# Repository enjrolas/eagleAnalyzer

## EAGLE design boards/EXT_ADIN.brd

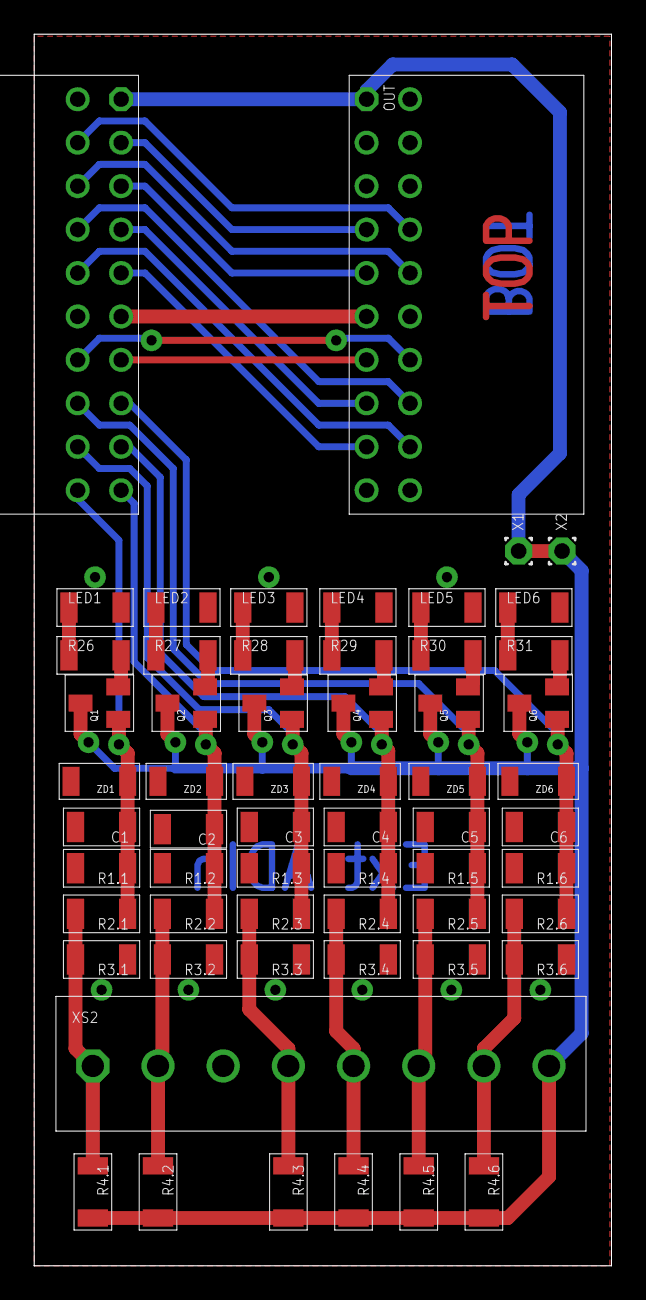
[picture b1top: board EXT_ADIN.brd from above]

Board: 2 copper layers, 33.8 x 72.0 mm, 59 parts (0 on the bottom side), 38 nets.

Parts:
C1, C2, C3, C4, C5, C6: 33n; 1206
IN: EF20; FE10-2WS
LED1, LED2: GREEN; 1206
LED3, LED4, LED5, LED6: YELLOW; 1206
OUT: MF20; ML20LS
Q1, Q2, Q3, Q4, Q5, Q6: BSS139; SOT23
R1.1, R1.2: 3k3; 1206
R1.3, R1.4, R1.5, R1.6: 39k; 1206
R2.1, R2.2: 6k8; 1206
R2.3, R2.4, R2.5, R2.6: 10k; 1206
R3.1, R3.5, R3.6, R4.1, R4.2, R4.3, R4.4: n.b.; 1206
R3.2: 560R; 1206
R3.3, R3.4, R4.5, R4.6: 3k6; 1206
R26, R27, R28, R29, R30, R31: 470R; 1206
X1, X2: T1.6/0.9
XS2: 1727078; SCR_381_8
ZD1, ZD2, ZD3, ZD4, ZD5, ZD6: SOD80

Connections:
3V3: IN.P$11, OUT.P$11
AI6: C1.1, IN.P$20, Q1.1, R1.1.1, R2.1.1, ZD1.C
AI7: C2.1, IN.P$19, Q2.1, R1.2.1, R2.2.1, ZD2.C
GND: C1.2, C2.2, C3.2, C4.2, C5.2, C6.2, IN.P$2, IN.P$12, LED1.2, LED2.2, LED3.2, LED4.2, LED5.2, LED6.2, OUT.P$2, OUT.P$12, R1.1.2, R1.2.2, R1.3.2, R1.4.2, R1.5.2, R1.6.2, R3.1.1, R3.2.1, R3.3.1, R3.4.1, R3.5.1, R3.6.1, XS2.P$3, ZD1.A, ZD2.A, ZD3.A, ZD4.A, ZD5.A, ZD6.A
unnamed: R2.2.2, R3.2.2, R4.2.1, XS2.P$2
unnamed: R2.3.2, R3.3.2, R4.3.1, XS2.P$4
unnamed: R2.1.2, R3.1.2, R4.1.1, XS2.P$1
unnamed: R2.4.2, R3.4.2, R4.4.1, XS2.P$5
unnamed: R2.5.2, R3.5.2, R4.5.1, XS2.P$6
unnamed: R2.6.2, R3.6.2, R4.6.1, XS2.P$7
unnamed: LED1.1, R26.1
unnamed: Q1.2, R26.2
unnamed: LED2.1, R27.1
unnamed: Q2.2, R27.2
unnamed: LED3.1, R28.1
unnamed: Q3.2, R28.2
unnamed: LED4.1, R29.1
unnamed: Q4.2, R29.2
unnamed: LED5.1, R30.1
unnamed: Q5.2, R30.2
unnamed: LED6.1, R31.1
unnamed: Q6.2, R31.2
PC0: C3.1, IN.P$18, Q3.1, R1.3.1, R2.3.1, ZD3.C
PC1: C4.1, IN.P$17, Q4.1, R1.4.1, R2.4.1, ZD4.C
PC2: C5.1, IN.P$16, Q5.1, R1.5.1, R2.5.1, ZD5.C
PC3: C6.1, IN.P$15, Q6.1, R1.6.1, R2.6.1, ZD6.C
PC4/SDA: IN.P$14, OUT.P$14
PC5/SCL: IN.P$13, OUT.P$13
PD0: IN.P$10, OUT.P$18
PD1: IN.P$9, OUT.P$17
PD2: IN.P$8, OUT.P$16
PD3: IN.P$7, OUT.P$15
PD4: IN.P$6, OUT.P$10
PD5: IN.P$5, OUT.P$9
PD6: IN.P$4, OUT.P$8
PD7: IN.P$3, OUT.P$7
VCC: Q1.3, Q2.3, Q3.3, Q4.3, Q5.3, Q6.3, R4.1.2, R4.2.2, R4.3.2, R4.4.2, R4.5.2, R4.6.2, X2.1, XS2.P$8
VIN: IN.P$1, OUT.P$1, X1.1

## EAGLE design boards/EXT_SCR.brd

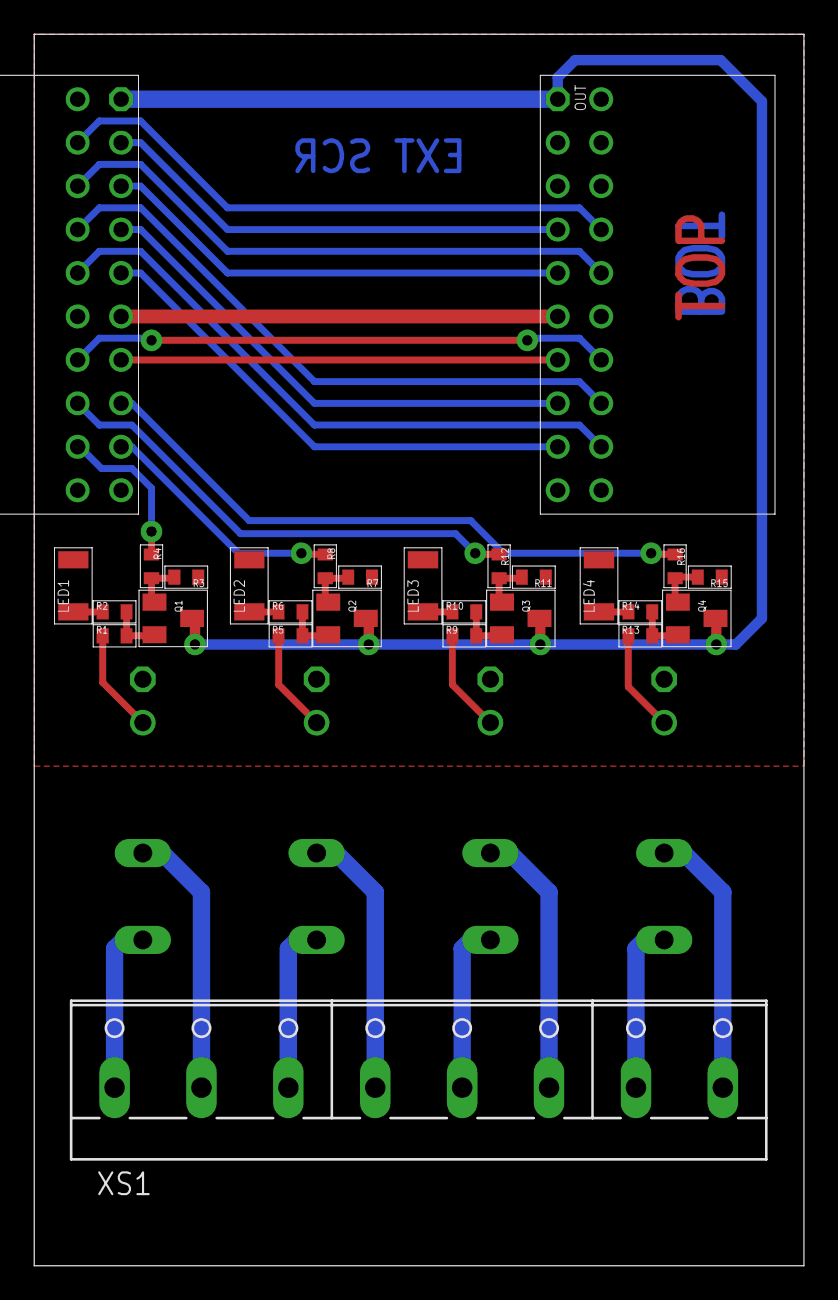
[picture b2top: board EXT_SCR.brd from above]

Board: 2 copper layers, 45.0 x 72.0 mm, 31 parts (0 on the bottom side), 41 nets.

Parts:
IN: EF20; FE10-2WS
LED1, LED2, LED3, LED4: LEDR; 1206
OUT: MF20; ML20LS
Q1, Q2, Q3, Q4: BC817; SOT23
R1, R5, R9, R13: 47R; 0603
R2, R6, R10, R14: 180R; 0603
R3, R7, R11, R15: 10k; 0603
R4, R8, R12, R16: 1k; 0603
SCR1, SCR2, SCR3, SCR4: S202S02; S202
XS1: 1729186; W237-8P

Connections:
3V3: IN.P$11, OUT.P$11
GND: IN.P$2, IN.P$12, LED1.2, LED2.2, LED3.2, LED4.2, OUT.P$2, OUT.P$12, R3.1, R7.1, R11.1, R15.1, SCR1.LED-, SCR2.LED-, SCR3.LED-, SCR4.LED-
unnamed: R1.1, SCR1.LED+
unnamed: LED1.1, R2.1
unnamed: Q1.2, R1.2, R2.2
unnamed: Q1.1, R3.2, R4.2
unnamed: R5.1, SCR2.LED+
unnamed: LED2.1, R6.1
unnamed: Q2.2, R5.2, R6.2
unnamed: Q2.1, R7.2, R8.2
unnamed: R9.1, SCR3.LED+
unnamed: LED3.1, R10.1
unnamed: Q3.2, R9.2, R10.2
unnamed: Q3.1, R11.2, R12.2
unnamed: R13.1, SCR4.LED+
unnamed: LED4.1, R14.1
unnamed: Q4.2, R13.2, R14.2
unnamed: Q4.1, R15.2, R16.2
unnamed: SCR1.AC1, XS1.1
unnamed: SCR1.AC2, XS1.2
unnamed: SCR2.AC1, XS1.3
unnamed: SCR2.AC2, XS1.4
unnamed: SCR3.AC1, XS1.5
unnamed: SCR3.AC2, XS1.6
unnamed: SCR4.AC2, XS1.8
unnamed: SCR4.AC1, XS1.7
PC0: IN.P$18, R4.1
PC1: IN.P$17, R8.1
PC2: IN.P$16, R12.1
PC3: IN.P$15, R16.1
PC4/SDA: IN.P$14, OUT.P$14
PC5/SCL: IN.P$13, OUT.P$13
PD0: IN.P$10, OUT.P$18
PD1: IN.P$9, OUT.P$17
PD2: IN.P$8, OUT.P$16
PD3: IN.P$7, OUT.P$15
PD4: IN.P$6, OUT.P$10
PD5: IN.P$5, OUT.P$9
PD6: IN.P$4, OUT.P$8
PD7: IN.P$3, OUT.P$7
VCC: IN.P$1, OUT.P$1, Q1.3, Q2.3, Q3.3, Q4.3

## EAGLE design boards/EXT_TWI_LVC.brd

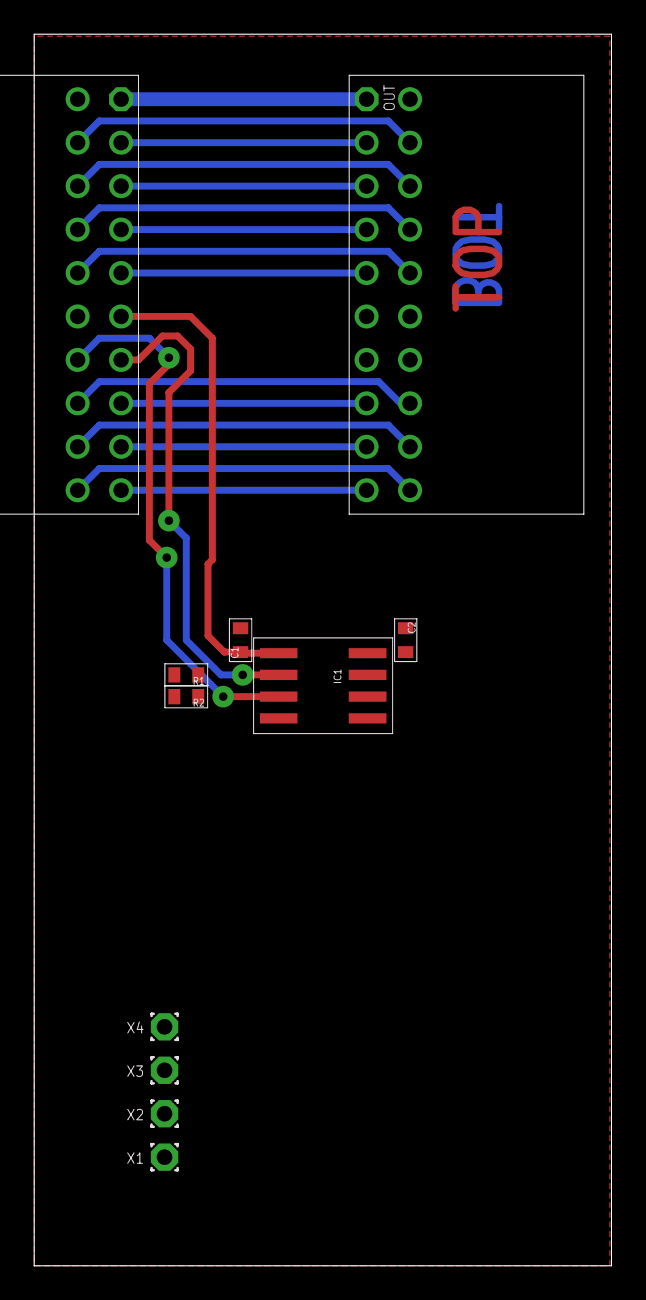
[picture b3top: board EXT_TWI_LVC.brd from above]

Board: 2 copper layers, 33.8 x 72.0 mm, 11 parts (0 on the bottom side), 22 nets.

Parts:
C1, C2: 100n; 0603
IC1: SOIC8
IN: EF20; FE10-2WS
OUT: MF20; ML20LS
R1, R2: 0603
X1, X2, X3, X4: T1.6/0.9

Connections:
GND: C1.2, C2.1, IC1.4, IN.P$2, IN.P$12, OUT.P$2, OUT.P$12, X1.1
unnamed: IN.P$20, OUT.P$20
unnamed: IN.P$19, OUT.P$19
unnamed: C2.2, IC1.8, OUT.P$11
PC0: IN.P$18, OUT.P$18
PC1: IN.P$17, OUT.P$17
PC2: IN.P$16, OUT.P$16
PC3: IN.P$15, OUT.P$15
PD0: IN.P$10, OUT.P$10
PD1: IN.P$9, OUT.P$9
PD2: IN.P$8, OUT.P$8
PD3: IN.P$7, OUT.P$7
PD4: IN.P$6, OUT.P$6
PD5: IN.P$5, OUT.P$5
PD6: IN.P$4, OUT.P$4
PD7: IN.P$3, OUT.P$3
SCLA: IC1.2, IN.P$13, R1.1, X3.1
SCLB: IC1.7, OUT.P$13
SDAA: IC1.3, IN.P$14, R2.1, X4.1
SDAB: IC1.6, OUT.P$14
VCCA: C1.1, IC1.1, IN.P$11, R1.2, R2.2, X2.1
VIN: IN.P$1, OUT.P$1

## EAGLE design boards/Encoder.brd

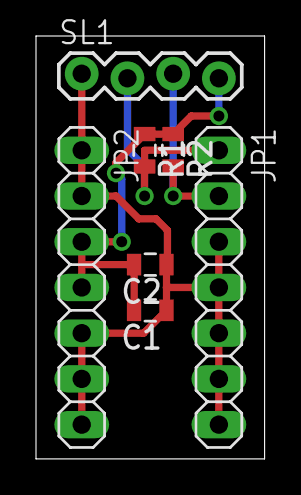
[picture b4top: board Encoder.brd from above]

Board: 2 copper layers, 12.7 x 23.5 mm, 7 parts (0 on the bottom side), 4 nets.

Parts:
C1: 47uF; 0805
C2: .1uF; 0805
JP1, JP2: 1X07
R1, R2: 4.7k; 0805
SL1: 1X04_LOCK

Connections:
GND: C1.1, C2.1, JP1.3, JP1.4, JP1.5, JP1.6, JP1.7, JP2.1, JP2.2, JP2.5, JP2.6, JP2.7, SL1.1
unnamed: JP1.1, R1.2, SL1.2
unnamed: JP1.2, R2.2, SL1.3
VCC: C1.2, C2.2, JP2.3, JP2.4, R1.1, R2.1, SL1.4

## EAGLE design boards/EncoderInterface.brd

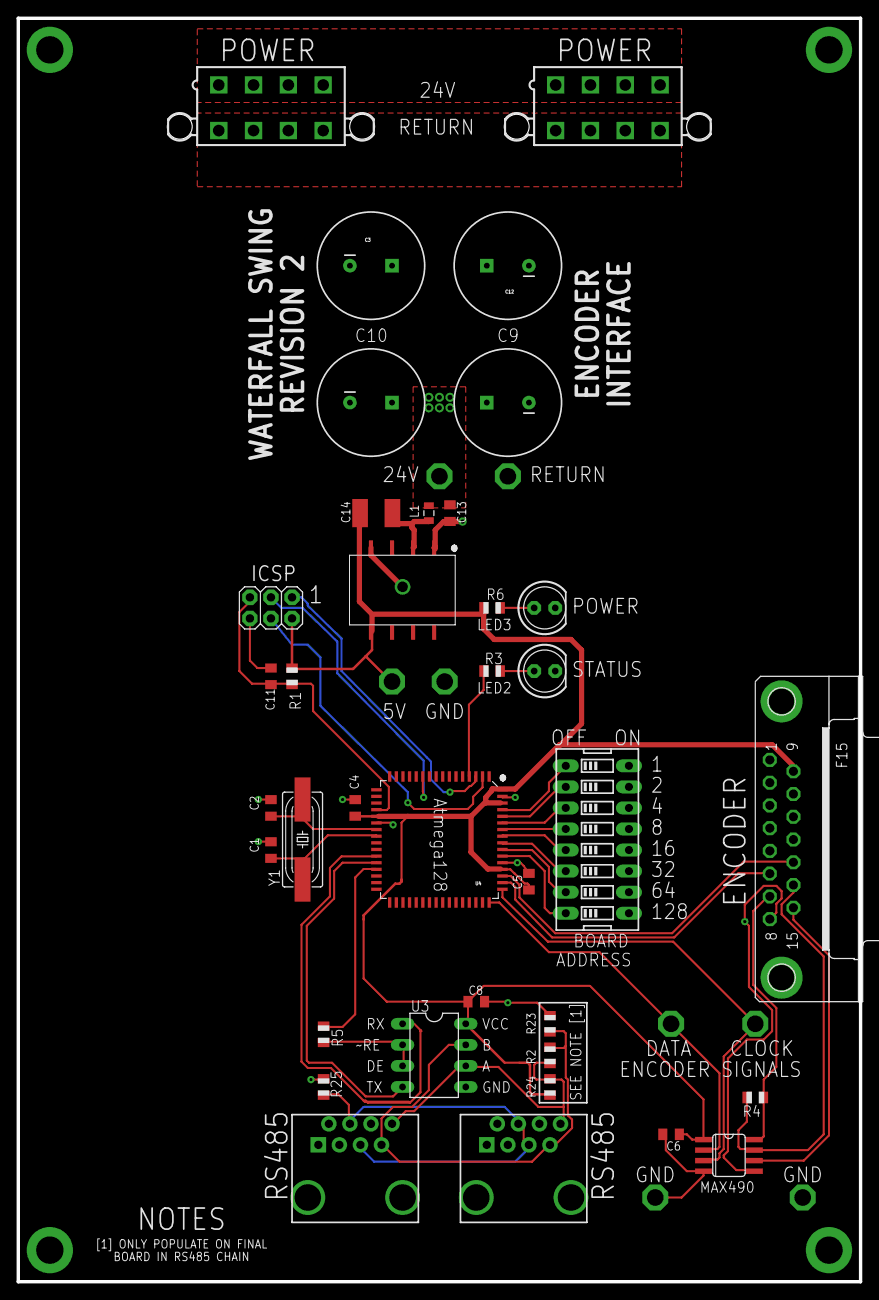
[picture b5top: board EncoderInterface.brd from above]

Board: 2 copper layers, 101.6 x 152.4 mm, 50 parts (1 on the bottom side), 37 nets.

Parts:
C1, C2: 31p; C0805K
C3, C9, C10, C12: 1000u; CPOL-RADIAL-1000UF-35V
C4, C5, C6, C8, C11: .1u; C0805K
C13: 4.7uF; C0805K
C14: 470pF,3kV; C1812
IC1: MAX490; SO08
ICSP: 2X03
J1, J2: RJ45-8PTH; RJ45-8
JP1, JP2, JP3, JP4: STAND-OFF
L1: 22uH; 0805
LED2, LED3: LED5MM
R1: 10k; R0805
R2, R4: 120; R0805
R3, R5, R6: 1k; R0805
R22, R25: 0; R0805
R23, R24: 560; R0805
REG: RECOM-R2S-2405-R; RECOM-SMD-8
SW1: DIPSWITCH-08
TP1, TP2, TP3, TP4, TP5, TP6, TP7, TP8: PTR1PAD1-20; P1-20
U3: SN75176BP; DIL08
U4: ATMEGA128-SMD; TQFP64_14X14MM
X1: F15HP
X3, X4: 5566-8
Y1: 16MHz; HC49UP

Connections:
5V: C4.1, C5.1, C6.1, C8.1, C14.2, IC1.1, ICSP.2, R1.1, R6.1, R24.2, REG.PIN5, TP3.TP, U3.8, U4.21, U4.52, U4.62, U4.64, X1.9
CLOCK: IC1.3, TP5.TP, U4.49
DATA: IC1.2, TP6.TP, U4.48
DMINUS: IC1.7, R4.2, X1.14
DPLUS: IC1.8, R4.1, X1.7
GND: C1.2, C2.2, C4.2, C5.2, C6.2, C8.2, C11.2, IC1.4, ICSP.6, LED2.K, LED3.K, R22.2, R23.1, R25.2, REG.PIN4, SW1.9, SW1.10, SW1.11, SW1.12, SW1.13, SW1.14, SW1.15, SW1.16, TP4.TP, TP7.TP, TP8.TP, U3.5, U4.22, U4.53, U4.63, X1.10, X1.G1, X1.G2
MISO: ICSP.1, U4.3
MOSI: ICSP.4, U4.2
unnamed: U3.1, U4.27
unnamed: J1.7, J2.7, R2.1, R23.2, U3.7
unnamed: R3.2, U4.4
unnamed: U3.4, U4.28
unnamed: C2.1, U4.23, Y1.2
unnamed: C1.1, U4.24, Y1.1
unnamed: LED2.A, R3.1
unnamed: LED3.A, R6.2
unnamed: C14.1, L1.1, REG.PIN2
unnamed: R5.2, U3.2, U3.3
unnamed: J1.8, J2.8, R2.2, R24.1, U3.6
unnamed: J1.4, J1.5, J2.4, J2.5, R25.1
unnamed: SW1.1, U4.61
unnamed: SW1.2, U4.60
unnamed: SW1.3, U4.59
unnamed: SW1.4, U4.58
unnamed: SW1.5, U4.57
unnamed: SW1.6, U4.56
unnamed: SW1.7, U4.55
unnamed: SW1.8, U4.54
unnamed: R5.1, U4.29
NRESET: C11.1, ICSP.5, R1.2, U4.20
RETURN: C3.2, C9.2, C10.2, C12.2, C13.2, R22.1, REG.PIN1, TP2.TP, X3.5, X3.6, X3.7, X3.8, X4.5, X4.6, X4.7, X4.8
SCK: ICSP.3, U4.11
ST: U4.50, X1.6
TMINUS: IC1.6, X1.15
TPLUS: IC1.5, X1.8
V+: C3.1, C9.1, C10.1, C12.1, C13.1, L1.2, TP1.TP, X3.1, X3.2, X3.3, X3.4, X4.1, X4.2, X4.3, X4.4
VR: U4.51, X1.13

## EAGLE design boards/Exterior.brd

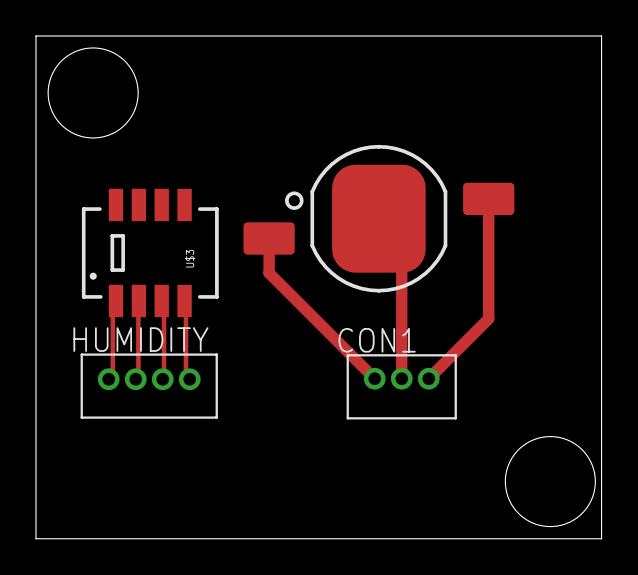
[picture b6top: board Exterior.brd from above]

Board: 2 copper layers, 31.4 x 27.9 mm, 4 parts (0 on the bottom side), 7 nets.

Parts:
CON1: B3B-ZR
HUMIDITY: B4B-ZR
U$1: LUXEONSMD; LUXEON
U$3: SHT1XSMD; SHT1X

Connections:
unnamed: CON1.2, U$1.S
unnamed: HUMIDITY.3, U$3.2
unnamed: HUMIDITY.4, U$3.1
unnamed: CON1.1, U$1.A
unnamed: CON1.3, U$1.C
unnamed: HUMIDITY.2, U$3.3
unnamed: HUMIDITY.1, U$3.4

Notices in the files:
parts and their libraries:
SparkFun-DigitalIC: Licensing: CC v3.0 Share-Alike You are welcome to use this library for commercial purposes.
